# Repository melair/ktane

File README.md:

# Keep Talking and Nobody Explodes - Physical Version

## Version Two

This is version two of my Keep Talking and Nobody Explodes physical bomb, you may refer to the `version-one` branch if you wish to see the first version progress.

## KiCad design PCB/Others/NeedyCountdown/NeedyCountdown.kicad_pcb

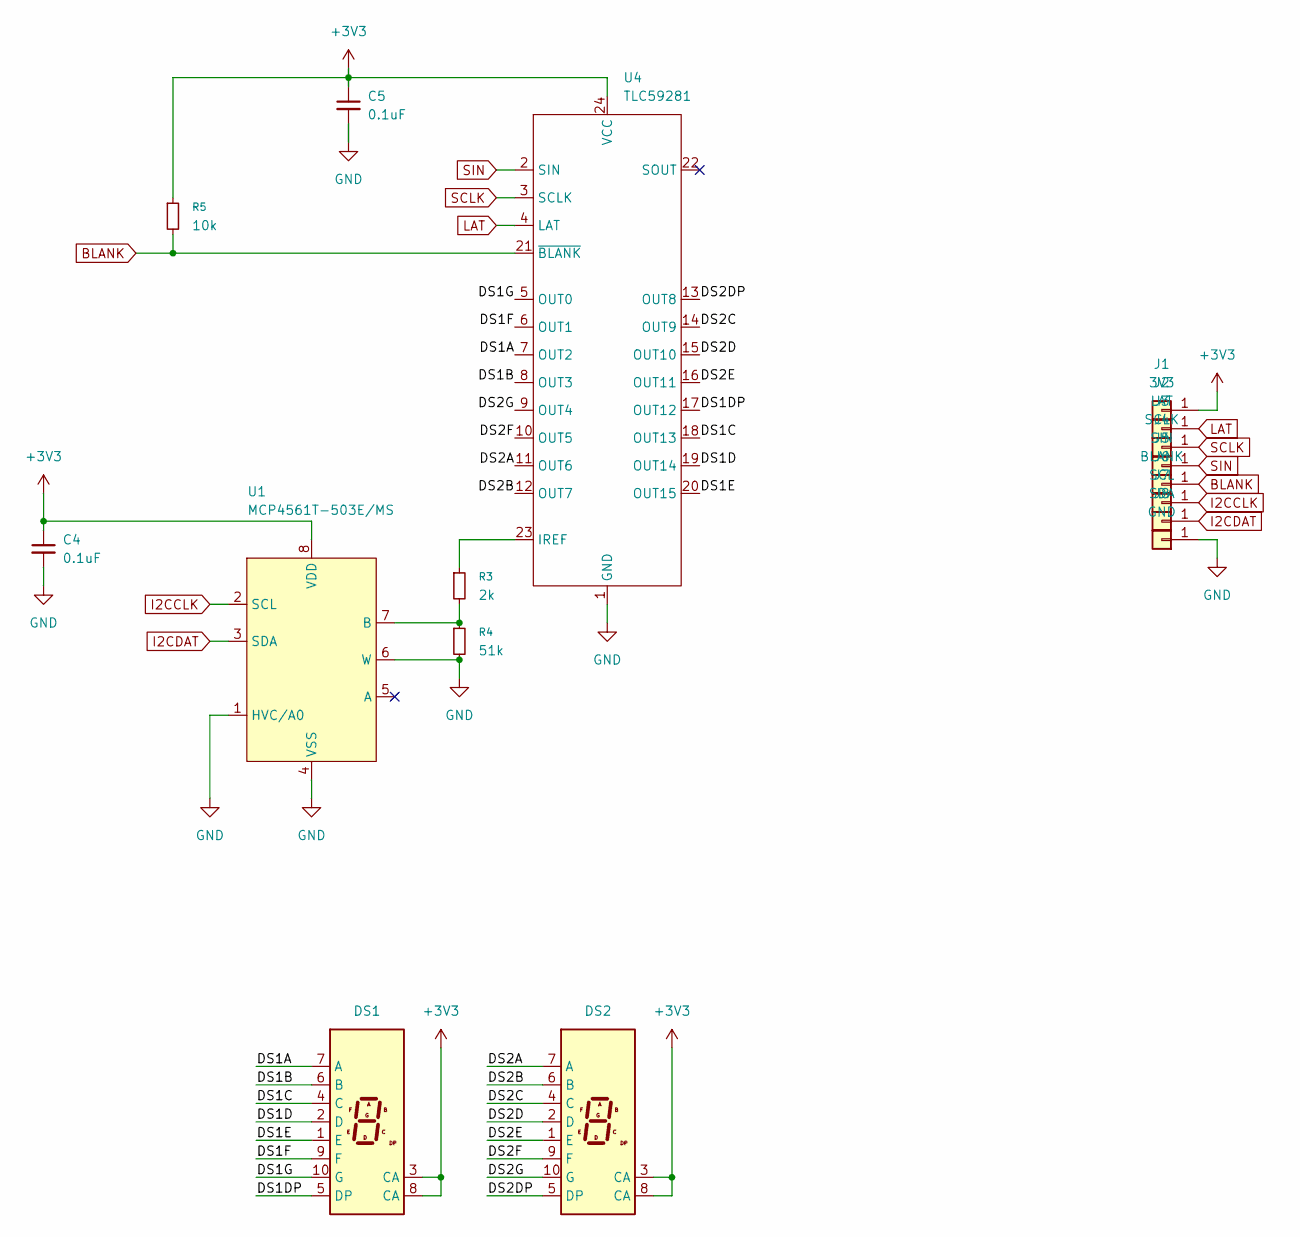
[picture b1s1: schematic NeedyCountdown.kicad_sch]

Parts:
C4, C5: 0.1uF; C_0603_1608Metric; DIGIKEY 1276-1005-1-ND
DS1, DS2: 5161 LED
J1: 3V3; Pad4x2; DIGIKEY NONE
J2: LAT; Pad4x2; DIGIKEY NONE
J3: SCLK; Pad4x2; DIGIKEY NONE
J4: SIN; Pad4x2; DIGIKEY NONE
J5: BLANK; Pad4x2; DIGIKEY NONE
J6: SCL; Pad4x2; DIGIKEY NONE
J7: SDA; Pad4x2; DIGIKEY NONE
J8: GND; Pad4x2; DIGIKEY NONE
R3: 2k; R_0603_1608Metric; DIGIKEY P2.00KHCT-ND
R4: 51k; R_0603_1608Metric; DIGIKEY P51.0KHCT-ND
R5: 10k; R_0603_1608Metric; DIGIKEY P10.0KHCT-ND
U1: MCP4561T-503E/MS; MSOP-8_3x3mm_P0.65mm
U4: TLC59281; SSOP-24_3.9x8.7mm_P0.635mm; DIGIKEY 296-25789-1-ND

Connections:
+3V3: C4.1, C5.1, DS1.3 (CA), DS1.8 (CA), DS2.3 (CA), DS2.8 (CA), J1.1 (Pin_1_1), R5.1, U1.8 (VDD), U4.24 (VCC)
/DS1A: DS1.7 (A), U4.7 (OUT2)
/DS1B: DS1.6 (B), U4.8 (OUT3)
/DS1C: DS1.4 (C), U4.18 (OUT13)
/DS1D: DS1.2 (D), U4.19 (OUT14)
/DS1DP: DS1.5 (DP), U4.17 (OUT12)
/DS1E: DS1.1 (E), U4.20 (OUT15)
/DS1F: DS1.9 (F), U4.6 (OUT1)
/DS1G: DS1.10 (G), U4.5 (OUT0)
/DS2A: DS2.7 (A), U4.11 (OUT6)
/DS2B: DS2.6 (B), U4.12 (OUT7)
/DS2C: DS2.4 (C), U4.14 (OUT9)
/DS2D: DS2.2 (D), U4.15 (OUT10)
/DS2DP: DS2.5 (DP), U4.13 (OUT8)
/DS2E: DS2.1 (E), U4.16 (OUT11)
/DS2F: DS2.9 (F), U4.10 (OUT5)
/DS2G: DS2.10 (G), U4.9 (OUT4)
BLANK: J5.1 (Pin_1_1), R5.2, U4.21 (~BLANK)
GND: C4.2, C5.2, J8.1 (Pin_1_1), R4.2, U1.1 (HVC/A0), U1.4 (VSS), U1.6 (W), U4.1 (GND)
I2CCLK: J6.1 (Pin_1_1), U1.2 (SCL)
I2CDAT: J7.1 (Pin_1_1), U1.3 (SDA)
LAT: J2.1 (Pin_1_1), U4.4 (LAT)
unnamed: R3.2, R4.1, U1.7 (B)
unnamed: R3.1, U4.23 (IREF)
SCLK: J3.1 (Pin_1_1), U4.3 (SCLK)
SIN: J4.1 (Pin_1_1), U4.2 (SIN)

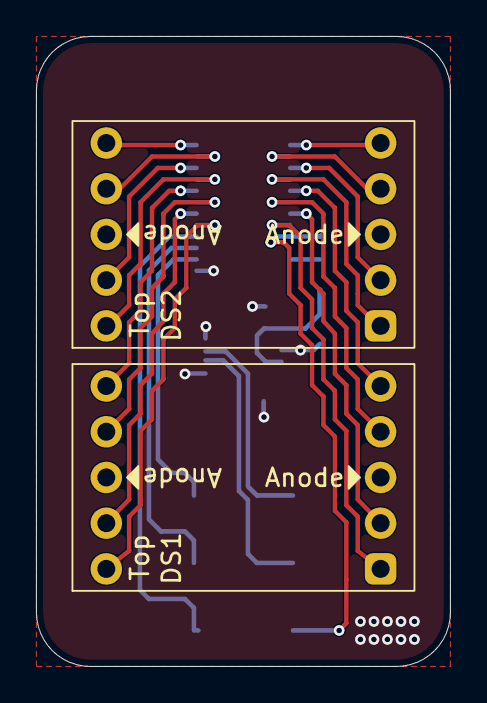
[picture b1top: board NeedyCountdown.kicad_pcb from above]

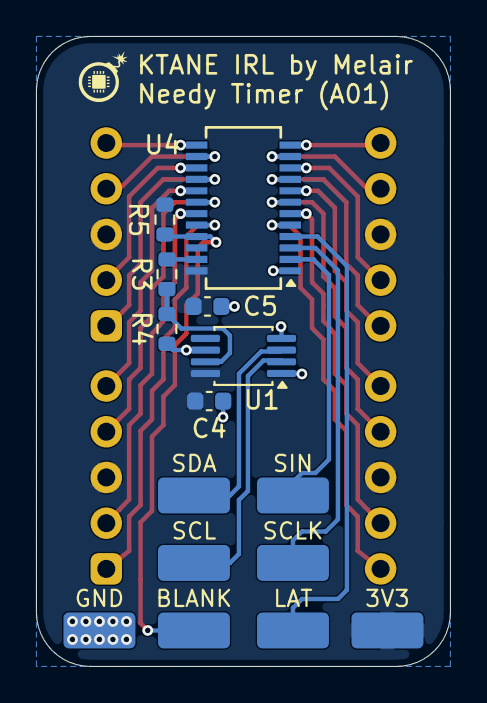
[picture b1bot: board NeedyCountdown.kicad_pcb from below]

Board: 2 copper layers, 23.0 x 35.0 mm, 17 parts (15 on the bottom side), 26 nets.

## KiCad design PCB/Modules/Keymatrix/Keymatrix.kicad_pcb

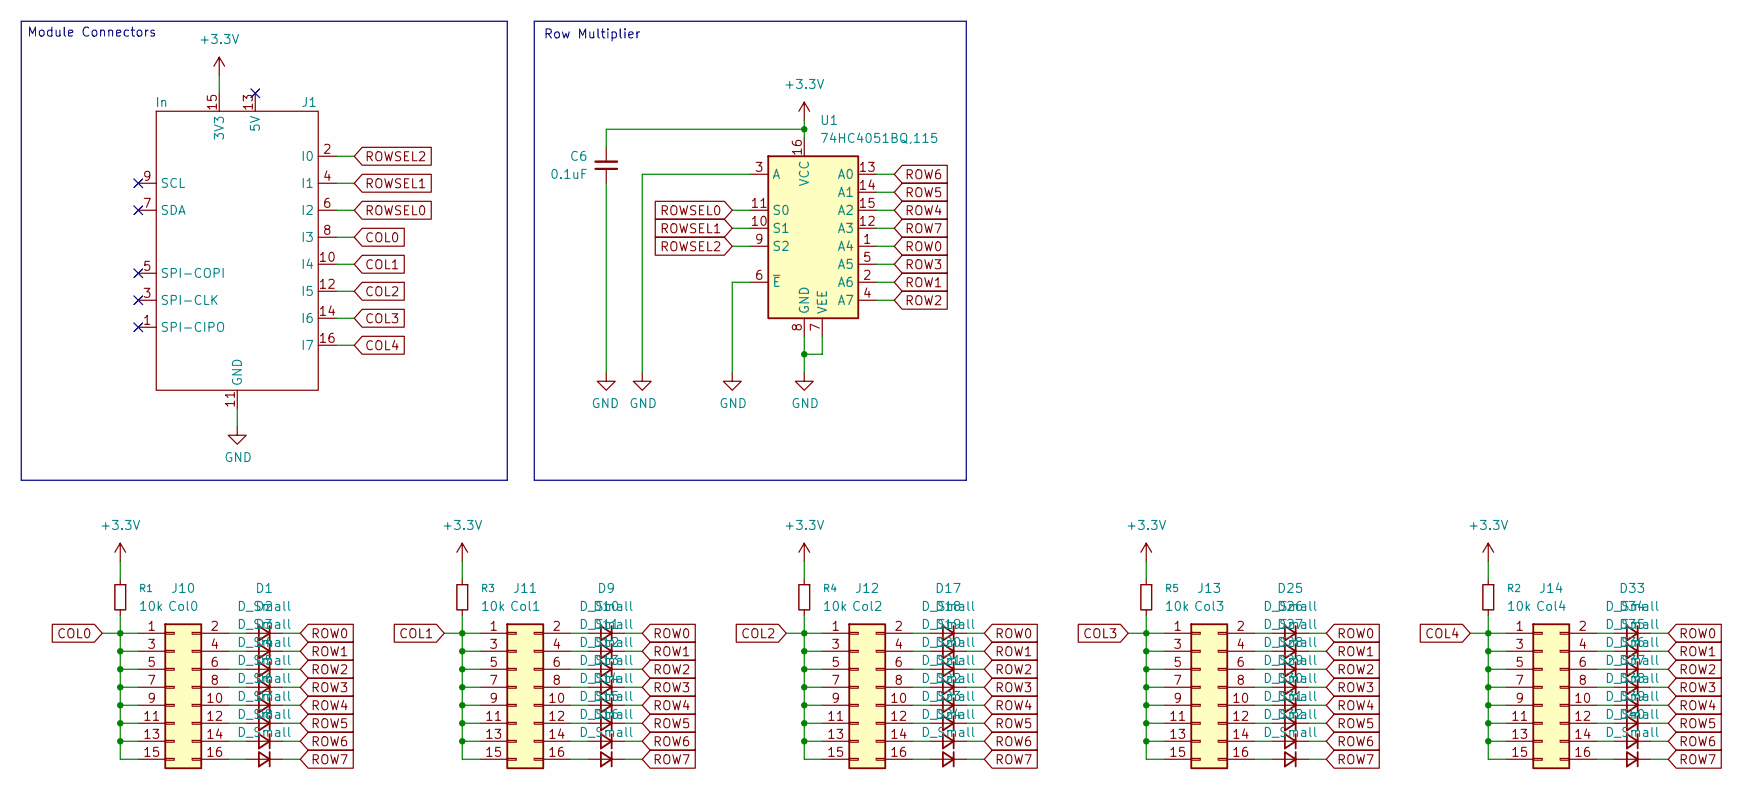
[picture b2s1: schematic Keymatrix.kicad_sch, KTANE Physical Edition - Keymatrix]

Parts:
C6: 0.1uF; C_0603_1608Metric
D1, D2, D3, D4, D5, D6, D7, D8, D9, D10, D11, D12, D13, D14, D15, D16, D17, D18, D19, D20, D21, D22, D23, D24, D25, D26, D27, D28, D29, D30, D31, D32, D33, D34, D35, D36, D37, D38, D39, D40: D_Small; D_0603_1608Metric
J1: In; KTANE Submodule Connector V2 - Short; DIGIKEY STOCK
J10: Col0; PinHeader_2x08_P2.54mm_Vertical
J11: Col1; PinHeader_2x08_P2.54mm_Vertical
J12: Col2; PinHeader_2x08_P2.54mm_Vertical
J13: Col3; PinHeader_2x08_P2.54mm_Vertical
J14: Col4; PinHeader_2x08_P2.54mm_Vertical
R1, R2, R3, R4, R5: 10k; R_0603_1608Metric
U1: 74HC4051BQ,115; DHVQFN-16-1EP_2.5x3.5mm_P0.5mm_EP1x2mm

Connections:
+3.3V: C6.2, J1.15 (3V3), R1.1, R2.1, R3.1, R4.1, R5.1, U1.16 (VCC)
COL0: J1.8 (I3), J10.1, J10.3, J10.5, J10.7, J10.9, J10.11, J10.13, J10.15, R1.2
COL1: J1.10 (I4), J11.1, J11.3, J11.5, J11.7, J11.9, J11.11, J11.13, J11.15, R3.2
COL2: J1.12 (I5), J12.1, J12.3, J12.5, J12.7, J12.9, J12.11, J12.13, J12.15, R4.2
COL3: J1.14 (I6), J13.1, J13.3, J13.5, J13.7, J13.9, J13.11, J13.13, J13.15, R5.2
COL4: J1.16 (I7), J14.1, J14.3, J14.5, J14.7, J14.9, J14.11, J14.13, J14.15, R2.2
GND: C6.1, J1.11 (GND), U1.3 (A), U1.6 (~E), U1.7 (VEE), U1.8 (GND)
unnamed: D1.2 (A), J10.2
unnamed: D2.2 (A), J10.4
unnamed: D3.2 (A), J10.6
unnamed: D4.2 (A), J10.8
unnamed: D5.2 (A), J10.10
unnamed: D6.2 (A), J10.12
unnamed: D7.2 (A), J10.14
unnamed: D8.2 (A), J10.16
unnamed: D9.2 (A), J11.2
unnamed: D10.2 (A), J11.4
unnamed: D11.2 (A), J11.6
unnamed: D12.2 (A), J11.8
unnamed: D13.2 (A), J11.10
unnamed: D14.2 (A), J11.12
unnamed: D15.2 (A), J11.14
unnamed: D16.2 (A), J11.16
unnamed: D17.2 (A), J12.2
unnamed: D18.2 (A), J12.4
unnamed: D19.2 (A), J12.6
unnamed: D20.2 (A), J12.8
unnamed: D21.2 (A), J12.10
unnamed: D22.2 (A), J12.12
unnamed: D23.2 (A), J12.14
unnamed: D24.2 (A), J12.16
unnamed: D25.2 (A), J13.2
unnamed: D26.2 (A), J13.4
unnamed: D27.2 (A), J13.6
unnamed: D28.2 (A), J13.8
unnamed: D29.2 (A), J13.10
unnamed: D30.2 (A), J13.12
unnamed: D31.2 (A), J13.14
unnamed: D32.2 (A), J13.16
unnamed: D33.2 (A), J14.2
unnamed: D34.2 (A), J14.4
unnamed: D35.2 (A), J14.6
unnamed: D36.2 (A), J14.8
unnamed: D37.2 (A), J14.10
unnamed: D38.2 (A), J14.12
unnamed: D39.2 (A), J14.14
unnamed: D40.2 (A), J14.16
ROW0: D1.1 (K), D9.1 (K), D17.1 (K), D25.1 (K), D33.1 (K), U1.1 (A4)
ROW1: D2.1 (K), D10.1 (K), D18.1 (K), D26.1 (K), D34.1 (K), U1.2 (A6)
ROW2: D3.1 (K), D11.1 (K), D19.1 (K), D27.1 (K), D35.1 (K), U1.4 (A7)
ROW3: D4.1 (K), D12.1 (K), D20.1 (K), D28.1 (K), D36.1 (K), U1.5 (A5)
ROW4: D5.1 (K), D13.1 (K), D21.1 (K), D29.1 (K), D37.1 (K), U1.15 (A2)
ROW5: D6.1 (K), D14.1 (K), D22.1 (K), D30.1 (K), D38.1 (K), U1.14 (A1)
ROW6: D7.1 (K), D15.1 (K), D23.1 (K), D31.1 (K), D39.1 (K), U1.13 (A0)
ROW7: D8.1 (K), D16.1 (K), D24.1 (K), D32.1 (K), D40.1 (K), U1.12 (A3)
ROWSEL0: J1.6 (I2), U1.11 (S0)
ROWSEL1: J1.4 (I1), U1.10 (S1)
ROWSEL2: J1.2 (I0), U1.9 (S2)

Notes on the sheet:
Module Connectors
Row Multiplier

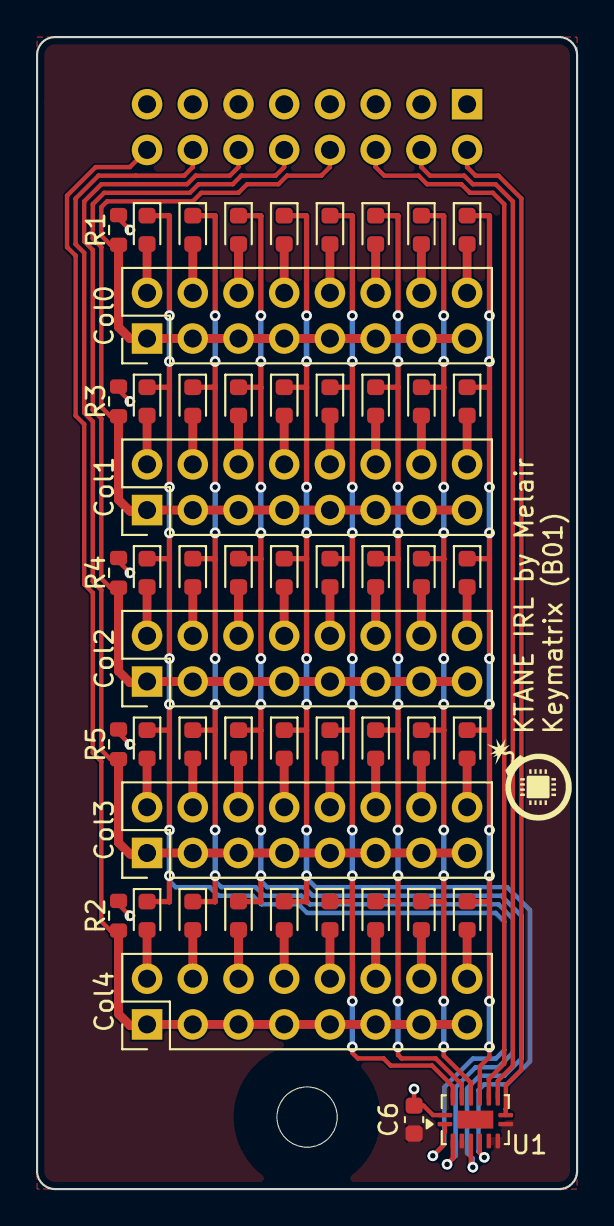
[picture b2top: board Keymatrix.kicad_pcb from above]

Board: 2 copper layers, 30.0 x 64.0 mm, 53 parts (0 on the bottom side), 58 nets.

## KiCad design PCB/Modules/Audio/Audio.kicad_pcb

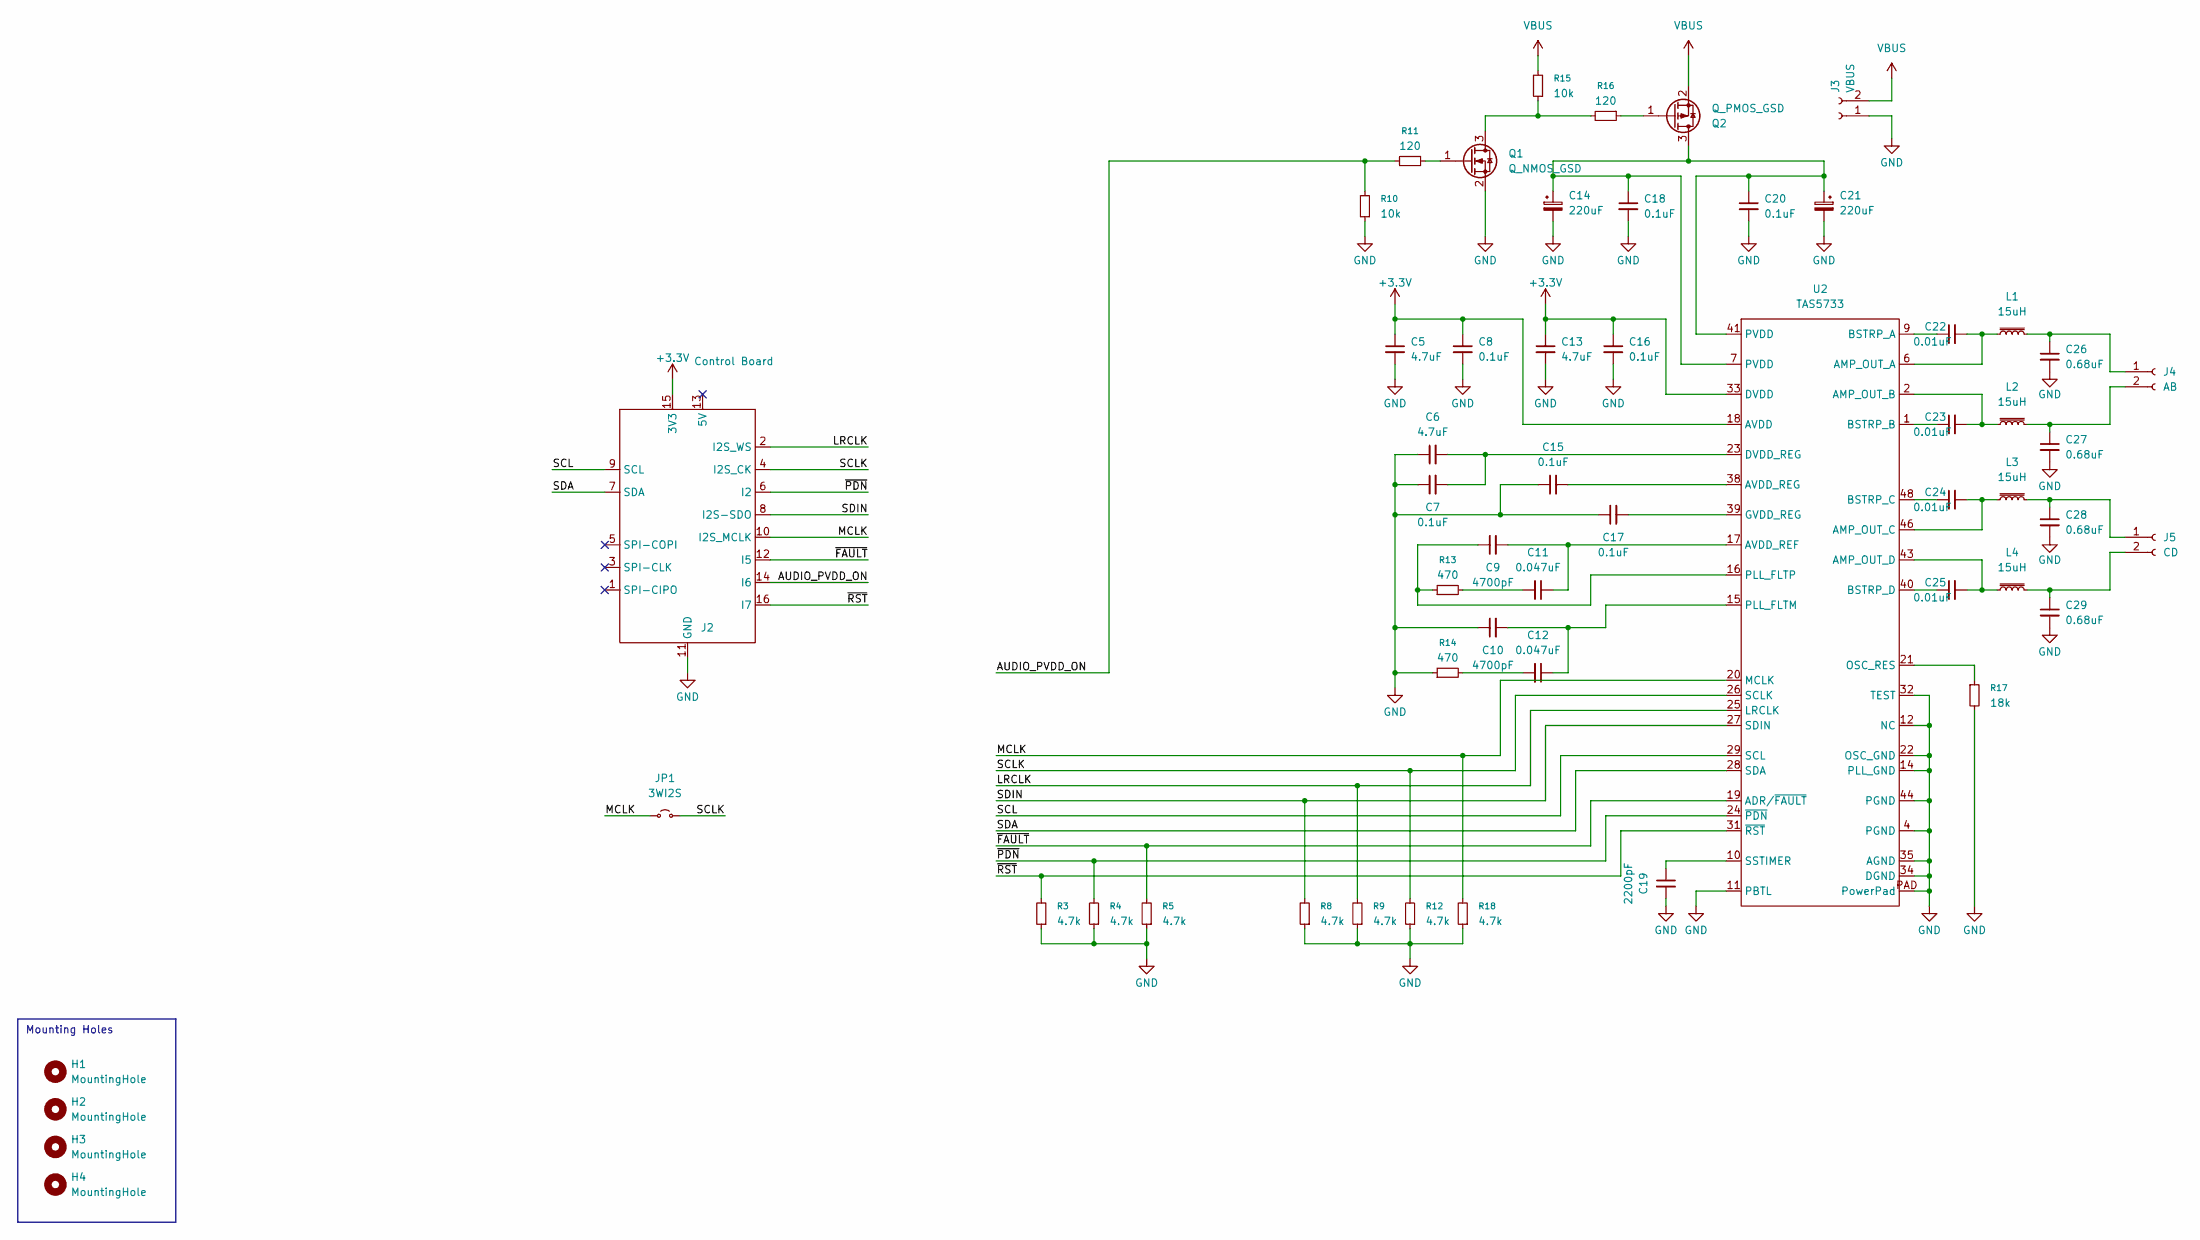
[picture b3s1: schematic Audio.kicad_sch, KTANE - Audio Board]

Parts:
C5, C6, C13: 4.7uF; C_0603_1608Metric; DIGIKEY 1276-2087-1-ND
C7, C8, C15, C16, C17: 0.1uF; C_0603_1608Metric; DIGIKEY 1276-1005-1-ND
C9, C10: 4700pF; C_0603_1608Metric; DIGIKEY 1276-1098-1-ND
C11, C12: 0.047uF; C_0603_1608Metric; DIGIKEY 1276-2079-1-ND
C14, C21: 220uF; CP_Elec_8x6.9; DIGIKEY PCE3839CT-ND
C18, C20: 0.1uF; C_0603_1608Metric; DIGIKEY 1276-CL10B104KB8NNNLCT-ND
C19: 2200pF; C_0603_1608Metric; DIGIKEY 1276-6530-1-ND
C22, C25: 0.01uF; C_0805_2012Metric; DIGIKEY 1276-1078-1-ND
C23, C24: 0.01uF; C_0603_1608Metric; DIGIKEY 1276-1009-1-ND
C26, C27, C28, C29: 0.68uF; C_0805_2012Metric; DIGIKEY 1276-7009-1-ND
H1, H2, H3, H4: MountingHole; MountingHole_3.2mm_M3_NoCopper; DIGIKEY NONE
J2: Control Board; PinHeader_2x08_P2.54mm_Vertical-Centered; DIGIKEY ALIEXPRESS/STOCK
J3: VBUS; AMASS_XT30PW-M_1x02_P2.50mm_Horizontal; DIGIKEY ALIEXPRESS/STOCK
J4: AB; JST_PH_B2B-PH-SM4-TB_1x02-1MP_P2.00mm_Vertical; DIGIKEY 455-B2B-PH-SM4-TBCT-ND
J5: CD; JST_PH_B2B-PH-SM4-TB_1x02-1MP_P2.00mm_Vertical; DIGIKEY 455-B2B-PH-SM4-TBCT-ND
JP1: 3WI2S; SolderJumper-2_P1.3mm_Open_Pad1.0x1.5mm
L1, L2, L3, L4: 15uH; L_APV_ANR8040; DIGIKEY 553-BWVS00808040150M00CT-ND
Q1: Q_NMOS_GSD; SOT-23-3; DIGIKEY 31-DMN2310U-7CT-ND
Q2: Q_PMOS_GSD; SOT-23; DIGIKEY 4518-SI2307ACT-ND
R3, R4, R5, R8, R9, R12, R18: 4.7k; R_0603_1608Metric; DIGIKEY P4.70KHCT-ND
R10, R15: 10k; R_0603_1608Metric; DIGIKEY P10.0KHCT-ND
R11, R16: 120; R_0603_1608Metric; DIGIKEY P120HCT-ND
R13, R14: 470; R_0603_1608Metric; DIGIKEY P470HCT-ND
R17: 18k; R_0603_1608Metric; DIGIKEY P18.0KHCT-ND
U2: TAS5733; HTSSOP-48_6.1x12.5mm_P0.5mm_EP_3.6x6.4; MOUSER 595-TAS5733LDCAR

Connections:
+3.3V: C5.1, C8.1, C13.1, C16.1, J2.15 (3V3), U2.18 (AVDD), U2.33 (DVDD)
/AUDIO_PVDD_ON: J2.14 (I6), R10.2, R11.2
/LRCLK: J2.2 (I2S_WS), R9.2, U2.25 (LRCLK)
/MCLK: J2.10 (I2S_MCLK), JP1.1 (A), R18.2, U2.20 (MCLK)
/SCL: J2.9 (SCL), U2.29 (SCL)
/SCLK: J2.4 (I2S_CK), JP1.2 (B), R12.2, U2.26 (SCLK)
/SDA: J2.7 (SDA), U2.28 (SDA)
/SDIN: J2.8 (I2S-SDO), R8.2, U2.27 (SDIN)
/~FAULT: J2.12 (I5), R5.2, U2.19 (ADR/~FAULT)
/~PDN: J2.6 (I2), R4.2, U2.24 (~PDN)
/~RST: J2.16 (I7), R3.2, U2.31 (~RST)
GND: C5.2, C6.1, C7.1, C8.2, C10.1, C13.2, C14.2, C15.1, C16.2, C17.1, C18.2, C19.2, C20.2, C21.2, C26.2, C27.2, C28.2, C29.2, J2.11 (GND), J3.1, Q1.2 (S), R3.1, R4.1, R5.1, R8.1, R9.1, R10.1, R12.1, R14.1, R17.2, R18.1, U2.4 (PGND), U2.5 (PGND), U2.11 (PBTL), U2.12 (NC), U2.13 (NC), U2.14 (PLL_GND), U2.22 (OSC_GND), U2.30 (NC), U2.32 (TEST), U2.34 (DGND), U2.35 (AGND), U2.36 (NC), U2.37 (NC), U2.44 (PGND), U2.45 (PGND), U2.PAD (PowerPad)
unnamed: C11.2, R13.2
unnamed: C12.2, R14.2
unnamed: C23.2, L2.2, U2.2 (AMP_OUT_B), U2.3 (AMP_OUT_B)
unnamed: C24.2, L3.2, U2.46 (AMP_OUT_C), U2.47 (AMP_OUT_C)
unnamed: C26.1, J4.1, L1.1
unnamed: C27.1, J4.2, L2.1
unnamed: C28.1, J5.1, L3.1
unnamed: C29.1, J5.2, L4.1
unnamed: Q1.3 (D), R15.1, R16.2
unnamed: Q1.1 (G), R11.1
unnamed: Q2.1 (G), R16.1
unnamed: C22.2, L1.2, U2.6 (AMP_OUT_A)
unnamed: C25.2, L4.2, U2.43 (AMP_OUT_D)
unnamed: C9.2, C11.1, U2.17 (AVDD_REF)
unnamed: C15.2, U2.38 (AVDD_REG)
unnamed: C22.1, U2.9 (BSTRP_A)
unnamed: C23.1, U2.1 (BSTRP_B)
unnamed: C24.1, U2.48 (BSTRP_C)
unnamed: C25.1, U2.40 (BSTRP_D)
unnamed: C6.2, C7.2, U2.23 (DVDD_REG)
unnamed: C17.2, U2.39 (GVDD_REG)
unnamed: R17.1, U2.21 (OSC_RES)
unnamed: C10.2, C12.1, U2.15 (PLL_FLTM)
unnamed: C9.1, R13.1, U2.16 (PLL_FLTP)
unnamed: C19.1, U2.10 (SSTIMER)
PVDD: C14.1, C18.1, C20.1, C21.1, Q2.3 (D), U2.7 (PVDD), U2.8 (PVDD), U2.41 (PVDD), U2.42 (PVDD)
VBUS: J3.2, Q2.2 (S), R15.2

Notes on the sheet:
Mounting Holes

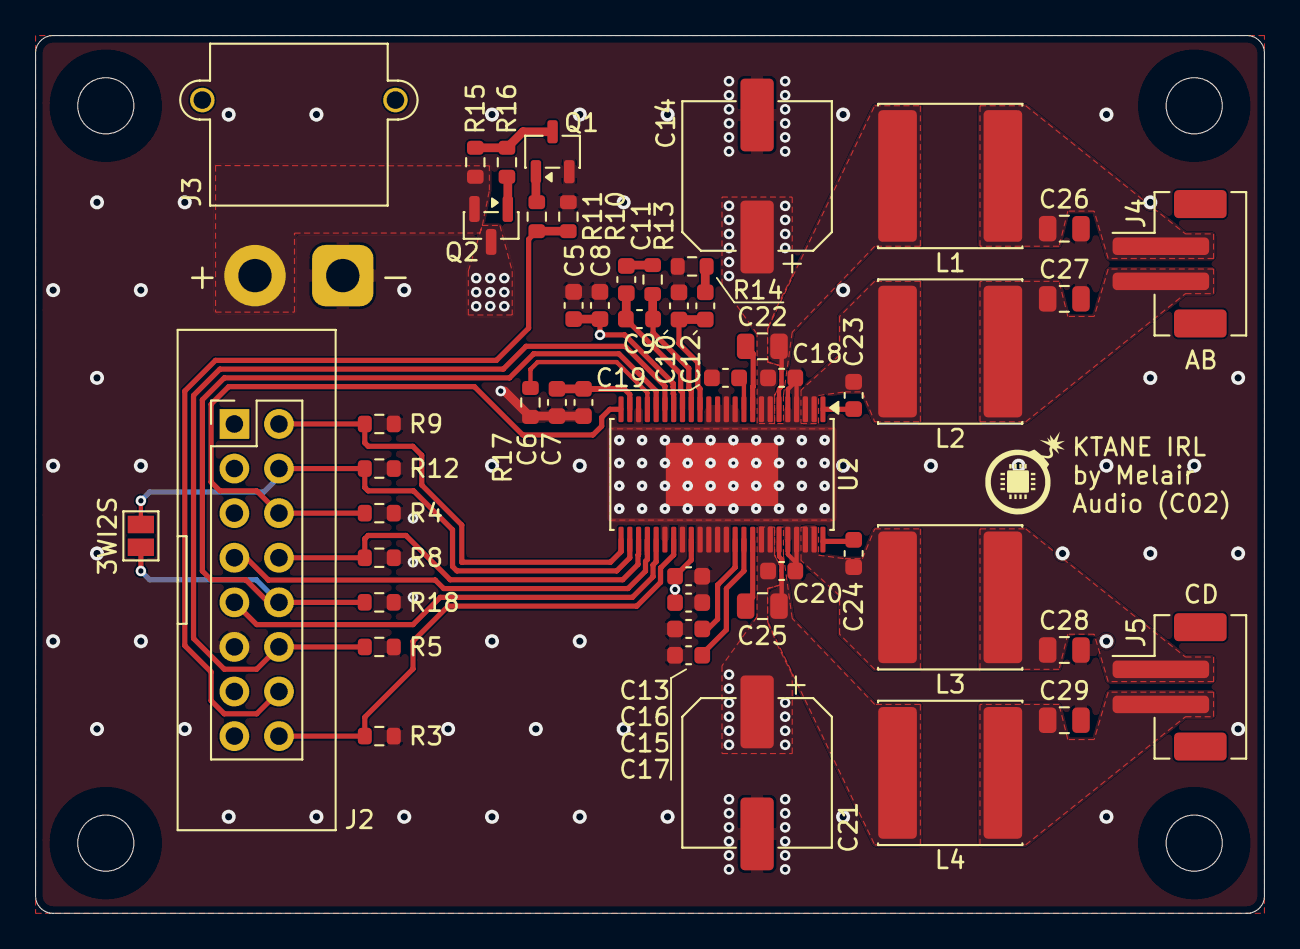
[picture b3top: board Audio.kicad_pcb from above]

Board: 4 copper layers, 70.0 x 50.0 mm, 55 parts (0 on the bottom side), 39 nets.

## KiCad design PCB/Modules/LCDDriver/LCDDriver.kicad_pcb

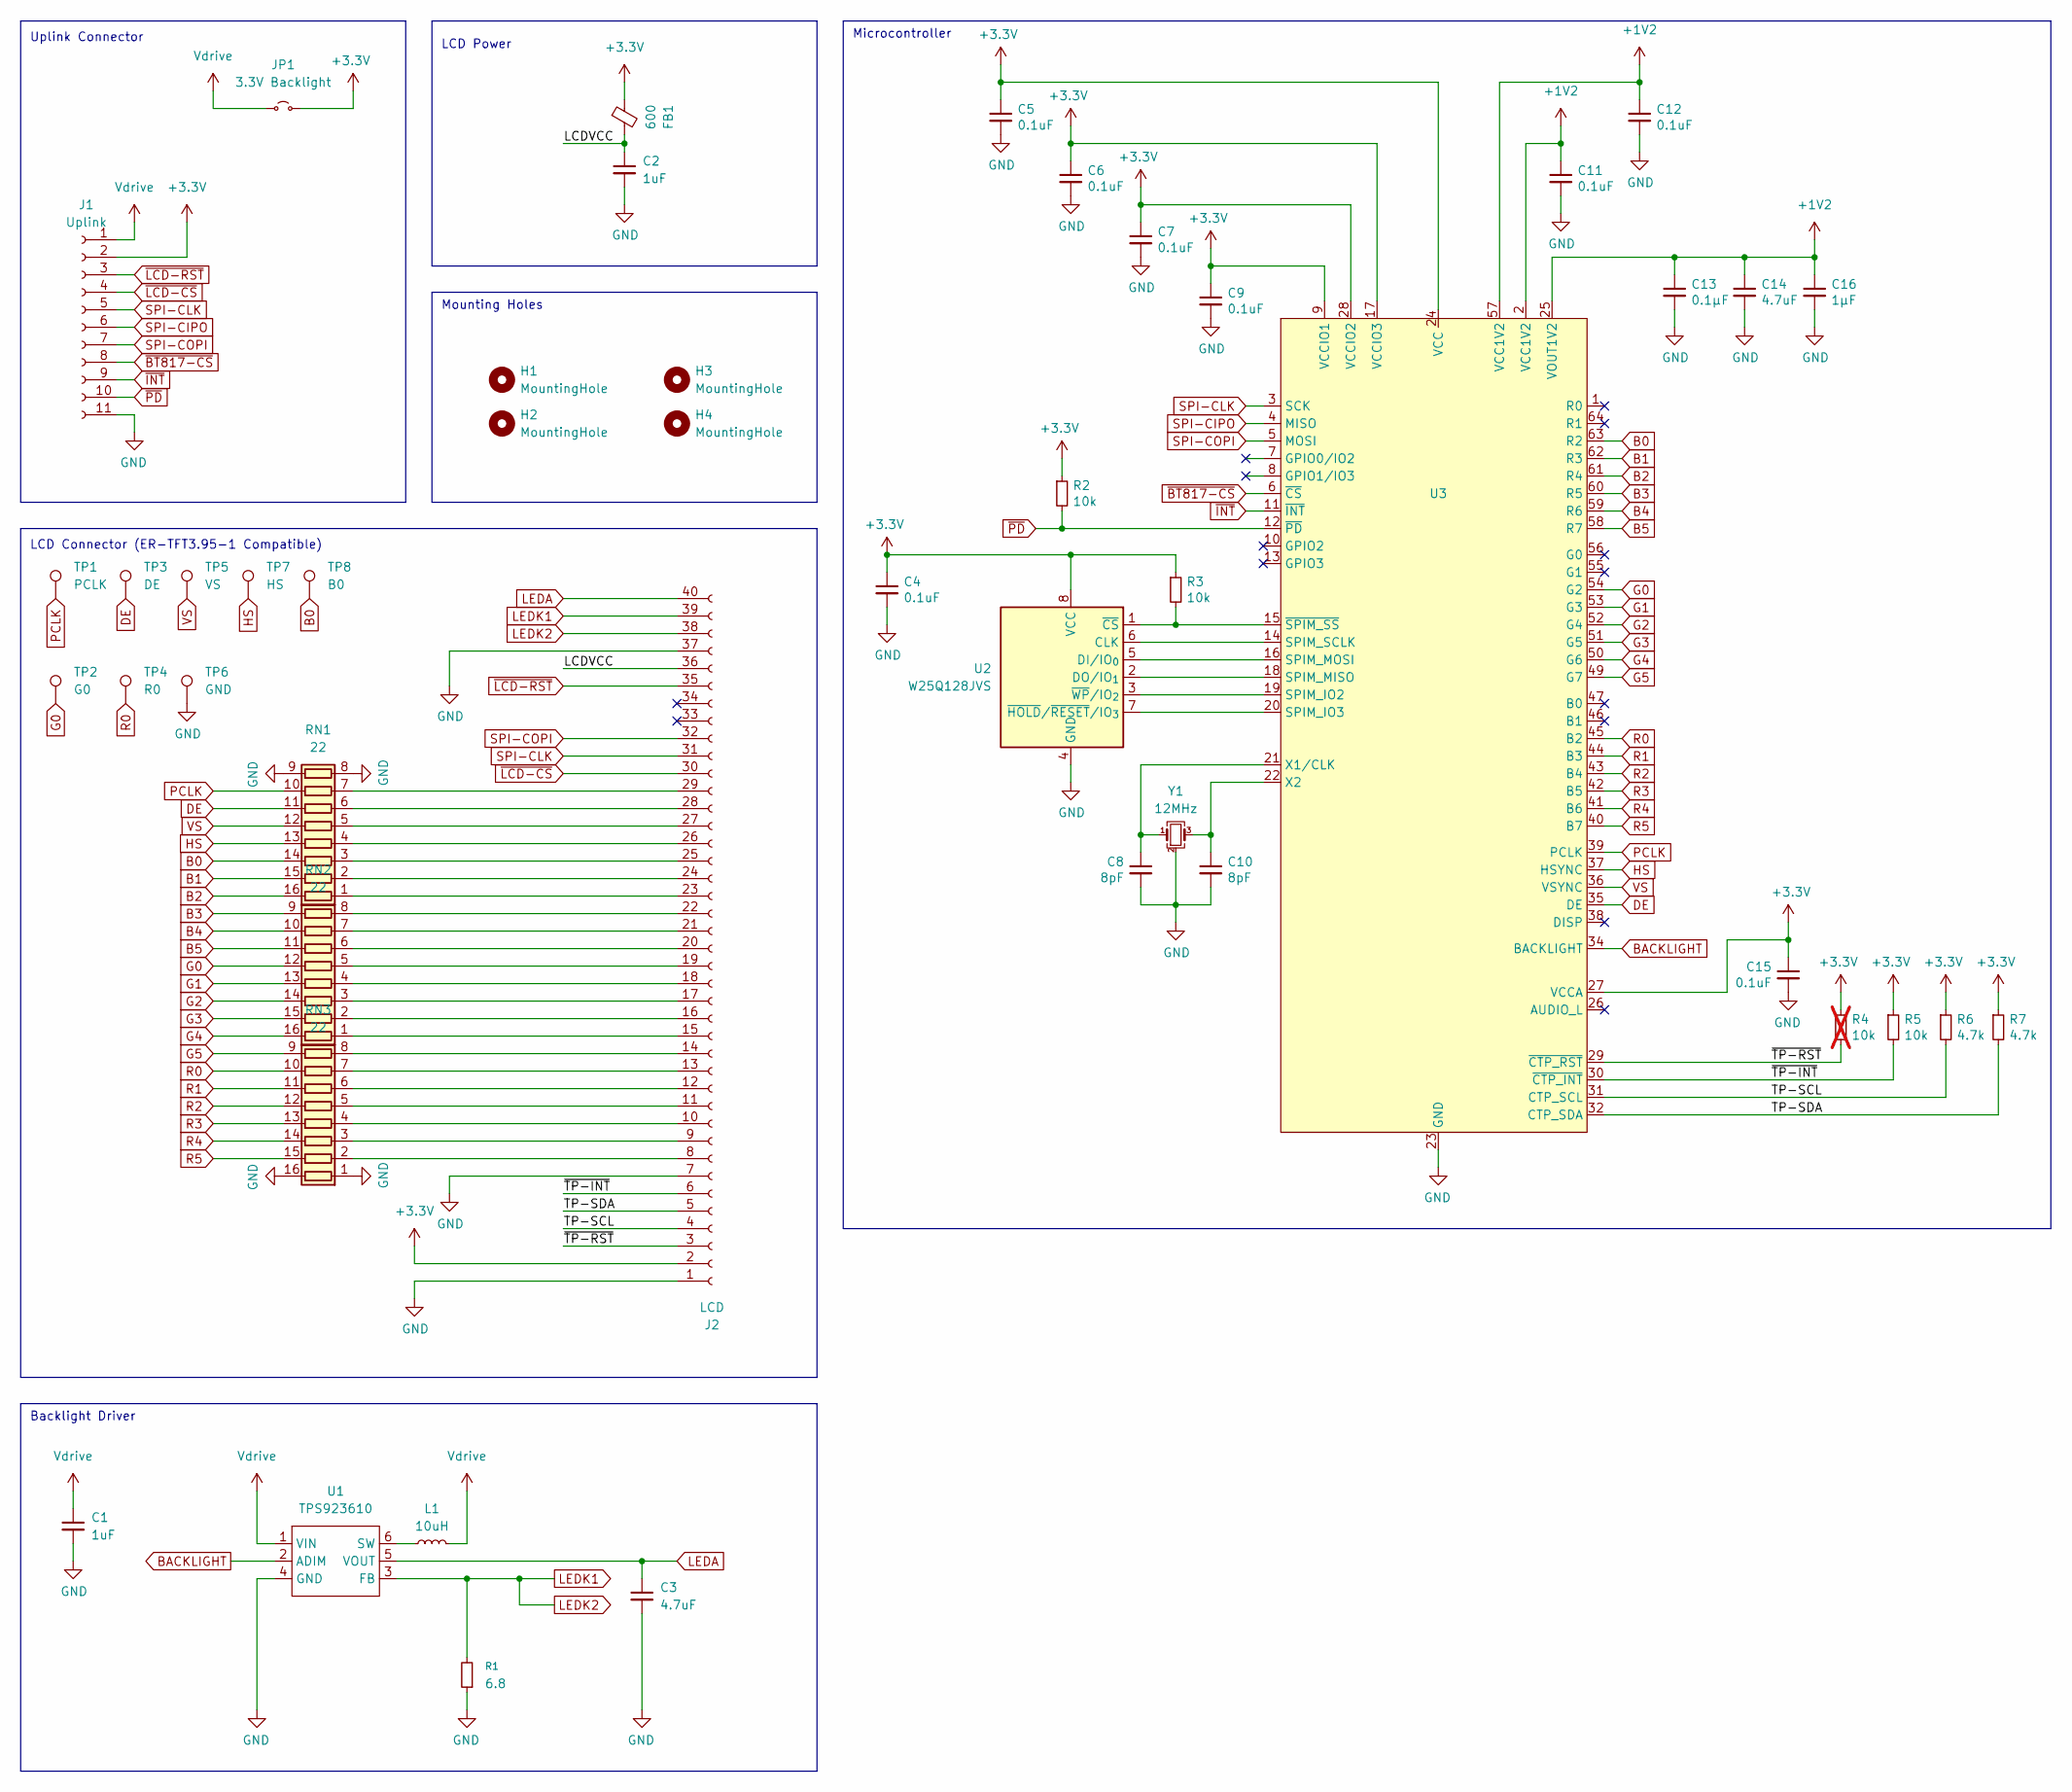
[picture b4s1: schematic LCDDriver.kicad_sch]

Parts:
C1, C2: 1uF; C_0603_1608Metric
C3: 4.7uF; C_0603_1608Metric; DIGIKEY 1276-6794-1-ND
C4, C5, C6, C7, C9, C11, C12, C15: 0.1uF; C_0603_1608Metric; DIGIKEY 1276-1005-1-ND
C8, C10: 8pF; C_0603_1608Metric; DIGIKEY 490-GCM1885C2A8R0BA16JCT-ND
C13: 0.1μF; C_0603_1608Metric; DIGIKEY 1276-1005-1-ND
C14: 4.7uF; C_0603_1608Metric; DIGIKEY 1276-2087-1-ND
C16: 1μF; C_0603_1608Metric; DIGIKEY 1276-1024-1-ND
FB1: 600; L_0603_1608Metric; DIGIKEY 490-1014-1-ND
H1, H2, H3, H4: MountingHole; MountingHole_3.2mm_M3_NoCopper
J1: Uplink; PinSocket_1x11_P2.54mm_Vertical
J2: LCD; AMPHENOL_F305-1A7H1-11040-E100; DIGIKEY 609-F305-1A7H1-11040-E100CT-ND
JP1: 3.3V Backlight; SolderJumper-2_P1.3mm_Open_RoundedPad1.0x1.5mm
L1: 10uH; L_1210_3225Metric; DIGIKEY 490-DFE322512F-100M=P2CT-ND
R1: 6.8; R_0603_1608Metric; DIGIKEY P6.8GCT-ND
R2, R3, R5: 10k; R_0603_1608Metric; DIGIKEY P10.0KHCT-ND
R4: 10k; R_0603_1608Metric; DIGIKEY P10.0KHCT-ND; not fitted
R6, R7: 4.7k; R_0603_1608Metric; DIGIKEY P4.70KHCT-ND
RN1, RN2, RN3: 22; R_Array_Convex_8x0602; DIGIKEY Y1000CT-ND / Y1220CT-ND
TP1: PCLK; TestPoint_Pad_D1.0mm
TP2: G0; TestPoint_Pad_D1.0mm
TP3: DE; TestPoint_Pad_D1.0mm
TP4: R0; TestPoint_Pad_D1.0mm
TP5: VS; TestPoint_Pad_D1.0mm
TP6: GND; TestPoint_Pad_D1.0mm
TP7: HS; TestPoint_Pad_D1.0mm
TP8: B0; TestPoint_Pad_D1.0mm
U1: TPS923610; Texas_R-PDSO-N6_DRL-6; DIGIKEY 296-TPS923610DRLRCT-ND
U2: W25Q128JVS; SOIC-8_5.3x5.3mm_P1.27mm
U3: VQFN-64-1EP_9x9mm_P0.5mm_EP5.4x5.4mm
Y1: 12MHz; Crystal_SMD_2520-4Pin_2.5x2.0mm; DIGIKEY 2151-R2520-12.000-8-1030-EXT-TRCT-ND

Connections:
+1V2: C11.1, C12.1, C13.1, C14.1, C16.1, U3.2 (VCC1V2), U3.25 (VOUT1V2), U3.57 (VCC1V2)
+3.3V: C4.1, C5.1, C6.1, C7.1, C9.1, C15.1, FB1.1, J1.2, J2.2, JP1.2 (B), R2.1, R3.1, R4.1, R5.1, R6.1, R7.1, U2.8 (VCC), U3.9 (VCCIO1), U3.17 (VCCIO3), U3.24 (VCC), U3.27 (VCCA), U3.28 (VCCIO2)
/LCDVCC: C2.1, FB1.2, J2.36
/TP-SCL: J2.4, R6.2, U3.31 (CTP_SCL)
/TP-SDA: J2.5, R7.2, U3.32 (CTP_SDA)
/~TP-INT: J2.6, R5.2, U3.30 (~CTP_INT)
/~TP-RST: J2.3, R4.2, U3.29 (~CTP_RST)
B0: RN1.14 (R3.2), TP8.1 (1_1), U3.63 (R2)
B1: RN1.15 (R2.2), U3.62 (R3)
B2: RN1.16 (R1.2), U3.61 (R4)
B3: RN2.9 (R8.2), U3.60 (R5)
B4: RN2.10 (R7.2), U3.59 (R6)
B5: RN2.11 (R6.2), U3.58 (R7)
BACKLIGHT: U1.2 (ADIM), U3.34 (BACKLIGHT)
DE: RN1.11 (R6.2), TP3.1 (1_1), U3.35 (DE)
G0: RN2.12 (R5.2), TP2.1 (1_1), U3.54 (G2)
G1: RN2.13 (R4.2), U3.53 (G3)
G2: RN2.14 (R3.2), U3.52 (G4)
G3: RN2.15 (R2.2), U3.51 (G5)
G4: RN2.16 (R1.2), U3.50 (G6)
G5: RN3.9 (R8.2), U3.49 (G7)
GND: C1.2, C2.2, C3.2, C4.2, C5.2, C6.2, C7.2, C8.2, C9.2, C10.2, C11.2, C12.2, C13.2, C14.2, C15.2, C16.2, J1.11, J2.1, J2.7, J2.37, R1.1, RN1.8 (R8.1), RN1.9 (R8.2), RN3.1 (R1.1), RN3.16 (R1.2), TP6.1 (1_1), U1.4 (GND), U2.4 (GND), U3.23 (GND), U3.33 (GND), U3.48 (GND), U3.65 (GND), Y1.2 (G), Y1.4 (G)
HS: RN1.13 (R4.2), TP7.1 (1_1), U3.37 (HSYNC)
LEDA: C3.1, J2.40, U1.5 (VOUT)
LEDK1: J2.38, J2.39, R1.2, U1.3 (FB)
unnamed: J2.8, RN3.2 (R2.1)
unnamed: J2.9, RN3.3 (R3.1)
unnamed: J2.10, RN3.4 (R4.1)
unnamed: J2.11, RN3.5 (R5.1)
unnamed: J2.12, RN3.6 (R6.1)
unnamed: J2.13, RN3.7 (R7.1)
unnamed: J2.14, RN3.8 (R8.1)
unnamed: J2.15, RN2.1 (R1.1)
unnamed: J2.16, RN2.2 (R2.1)
unnamed: J2.17, RN2.3 (R3.1)
unnamed: J2.18, RN2.4 (R4.1)
unnamed: J2.19, RN2.5 (R5.1)
unnamed: J2.20, RN2.6 (R6.1)
unnamed: J2.21, RN2.7 (R7.1)
unnamed: J2.22, RN2.8 (R8.1)
unnamed: J2.23, RN1.1 (R1.1)
unnamed: J2.24, RN1.2 (R2.1)
unnamed: J2.25, RN1.3 (R3.1)
unnamed: J2.26, RN1.4 (R4.1)
unnamed: J2.27, RN1.5 (R5.1)
unnamed: J2.28, RN1.6 (R6.1)
unnamed: J2.29, RN1.7 (R7.1)
unnamed: L1.1, U1.6 (SW)
unnamed: U2.6 (CLK), U3.14 (SPIM_SCLK)
unnamed: U2.5 (DI/IO_{0}), U3.16 (SPIM_MOSI)
unnamed: U2.2 (DO/IO_{1}), U3.18 (SPIM_MISO)
unnamed: R3.2, U2.1 (~CS), U3.15 (~SPIM_SS)
unnamed: U2.7 (~HOLD/~RESET/IO_{3}), U3.20 (SPIM_IO3)
unnamed: U2.3 (~WP/IO_{2}), U3.19 (SPIM_IO2)
unnamed: C8.1, U3.21 (X1/CLK), Y1.1
unnamed: C10.1, U3.22 (X2), Y1.3
PCLK: RN1.10 (R7.2), TP1.1 (1_1), U3.39 (PCLK)
R0: RN3.10 (R7.2), TP4.1 (1_1), U3.45 (B2)
R1: RN3.11 (R6.2), U3.44 (B3)
R2: RN3.12 (R5.2), U3.43 (B4)
R3: RN3.13 (R4.2), U3.42 (B5)
R4: RN3.14 (R3.2), U3.41 (B6)
R5: RN3.15 (R2.2), U3.40 (B7)
SPI-CIPO: J1.6, U3.4 (MISO)
SPI-CLK: J1.5, J2.31, U3.3 (SCK)
SPI-COPI: J1.7, J2.32, U3.5 (MOSI)
VS: RN1.12 (R5.2), TP5.1 (1_1), U3.36 (VSYNC)
Vdrive: C1.1, J1.1, JP1.1 (A), L1.2, U1.1 (VIN)
~BT817-CS: J1.8, U3.6 (~CS)
~INT: J1.9, U3.11 (~INT)
~LCD-CS: J1.4, J2.30
~LCD-RST: J1.3, J2.35
~PD: J1.10, R2.2, U3.12 (~PD)

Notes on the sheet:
Uplink Connector
Microcontroller
LCD Power
LCD Connector (ER-TFT3.95-1 Compatible)
Mounting Holes
Backlight Driver

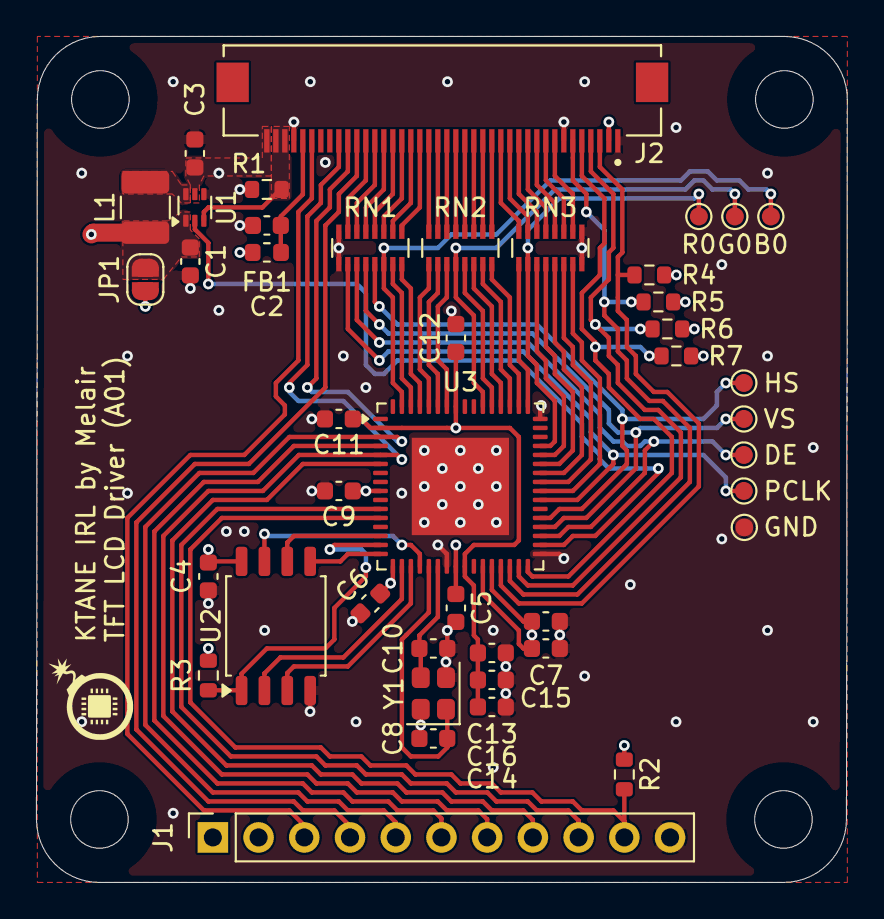
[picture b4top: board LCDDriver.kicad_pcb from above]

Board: 4 copper layers, 45.0 x 47.0 mm, 47 parts (0 on the bottom side), 73 nets.
